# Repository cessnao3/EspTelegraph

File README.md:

# EspTelegraph

Hosts several tasks, including:

* Connecting to a wireless network
* Providing a temrinal console via serial to allow setting wifi parameters and testing morse output
* Hosting an HTTP server, allowing users to input morse commands
* Translating ASCII text into morse commands to send via discrete output
* Holding a queue of messages, allowing a certain number of messages to be held in reserve

The web server contains an API that allows external programs to request morse messages via the `/api` endpoint with an HTTP GET request. API endpoint options include:

* `msg`: The message to output via morse.
* `unit_millis`: The number of milliseconds per morse unit. By default, this is 50 ms if this option is either omitted or <= 0.

Morse units are translated such that a dot is one unit on, one unit off, a dash is three units on, one unit off, a space between words is seven units off, and the space between characters is three units off.

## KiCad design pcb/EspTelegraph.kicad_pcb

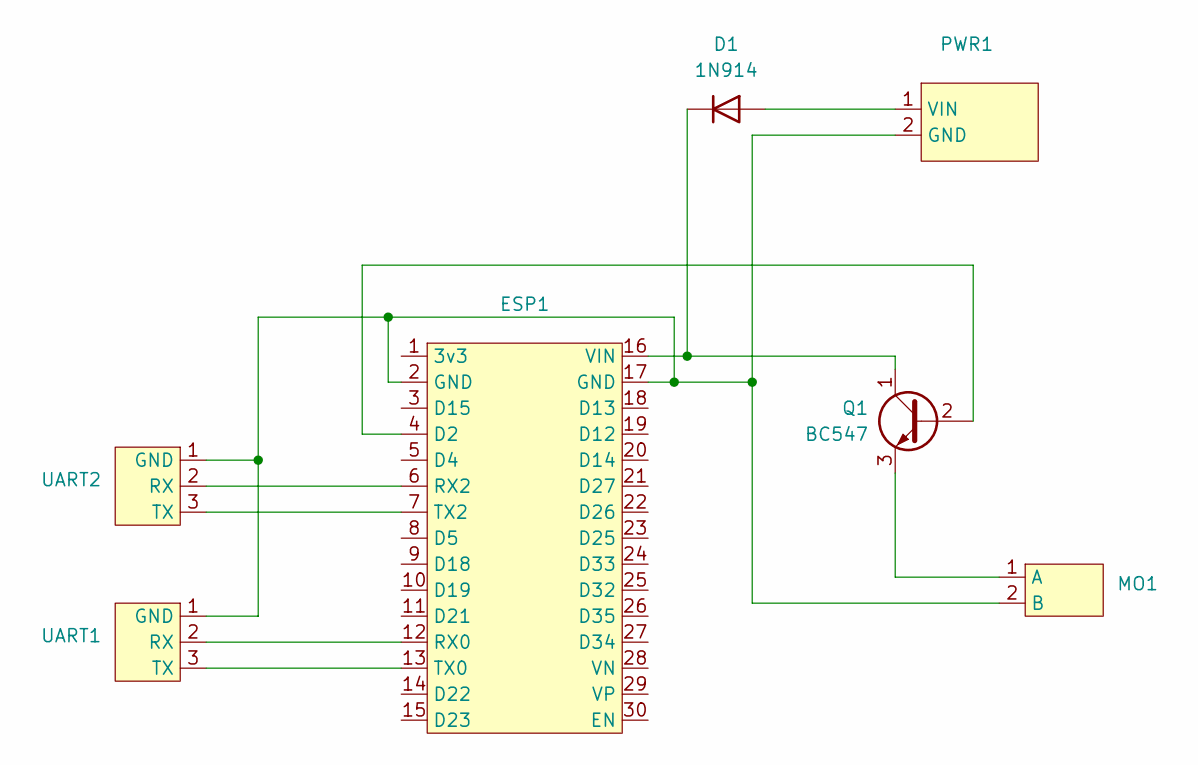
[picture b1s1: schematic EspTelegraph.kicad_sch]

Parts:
D1: 1N914; D_DO-35_SOD27_P7.62mm_Horizontal
ESP1: Esp32Dev
MO1: MorseOutput
PWR1: PowerInput
Q1: BC547; TO-92_Inline
UART1, UART2: UART

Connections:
unnamed: D1.2 (A), PWR1.1 (VIN)
unnamed: D1.1 (K), ESP1.16 (VIN), Q1.1 (C)
unnamed: ESP1.4 (D2), Q1.2 (B)
unnamed: ESP1.12 (RX0), UART1.2 (RX)
unnamed: ESP1.6 (RX2), UART2.2 (RX)
unnamed: ESP1.13 (TX0), UART1.3 (TX)
unnamed: ESP1.7 (TX2), UART2.3 (TX)
unnamed: MO1.1 (A), Q1.3 (E)
unnamed: ESP1.2 (GND), ESP1.17 (GND), MO1.2 (B), PWR1.2 (GND), UART1.1 (GND), UART2.1 (GND)

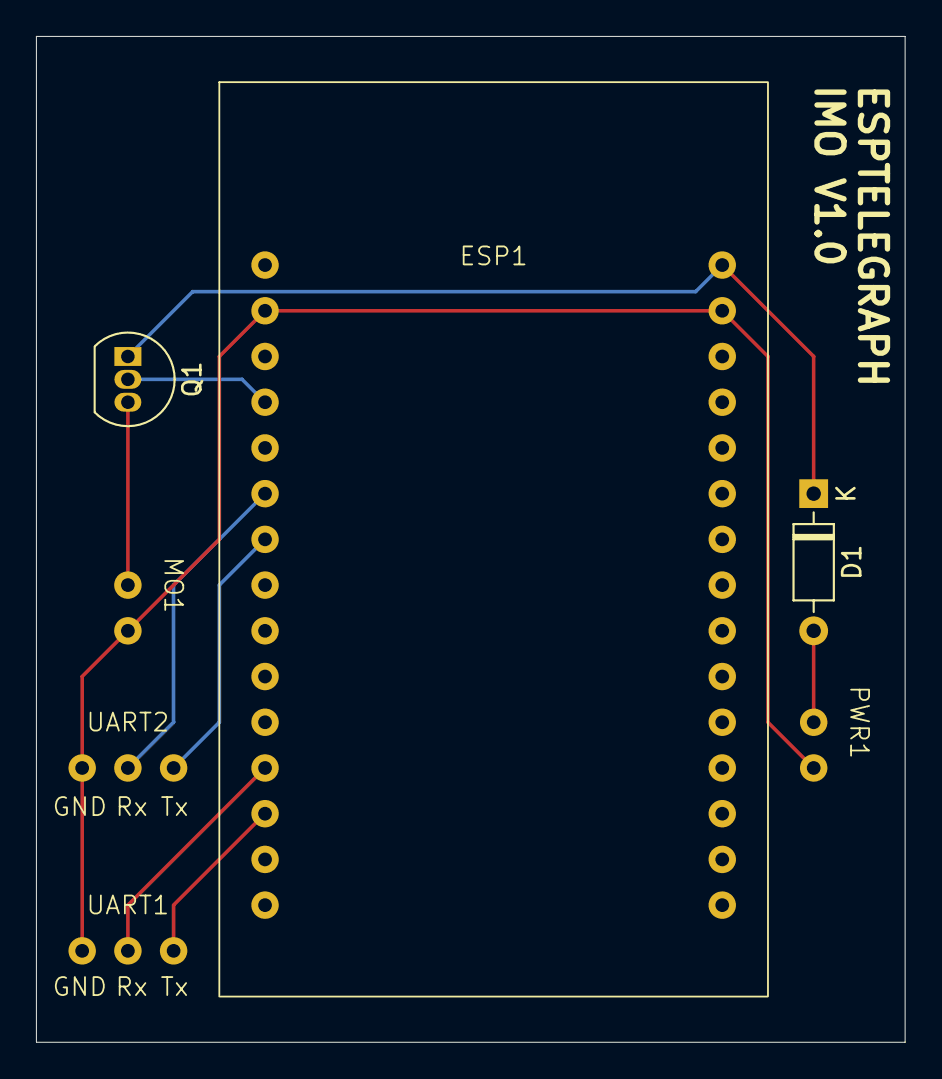
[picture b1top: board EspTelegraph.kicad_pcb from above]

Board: 2 copper layers, 48.3 x 55.9 mm, 7 parts (0 on the bottom side), 9 nets.

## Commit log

2024-04-14 Initial PCB Commit
